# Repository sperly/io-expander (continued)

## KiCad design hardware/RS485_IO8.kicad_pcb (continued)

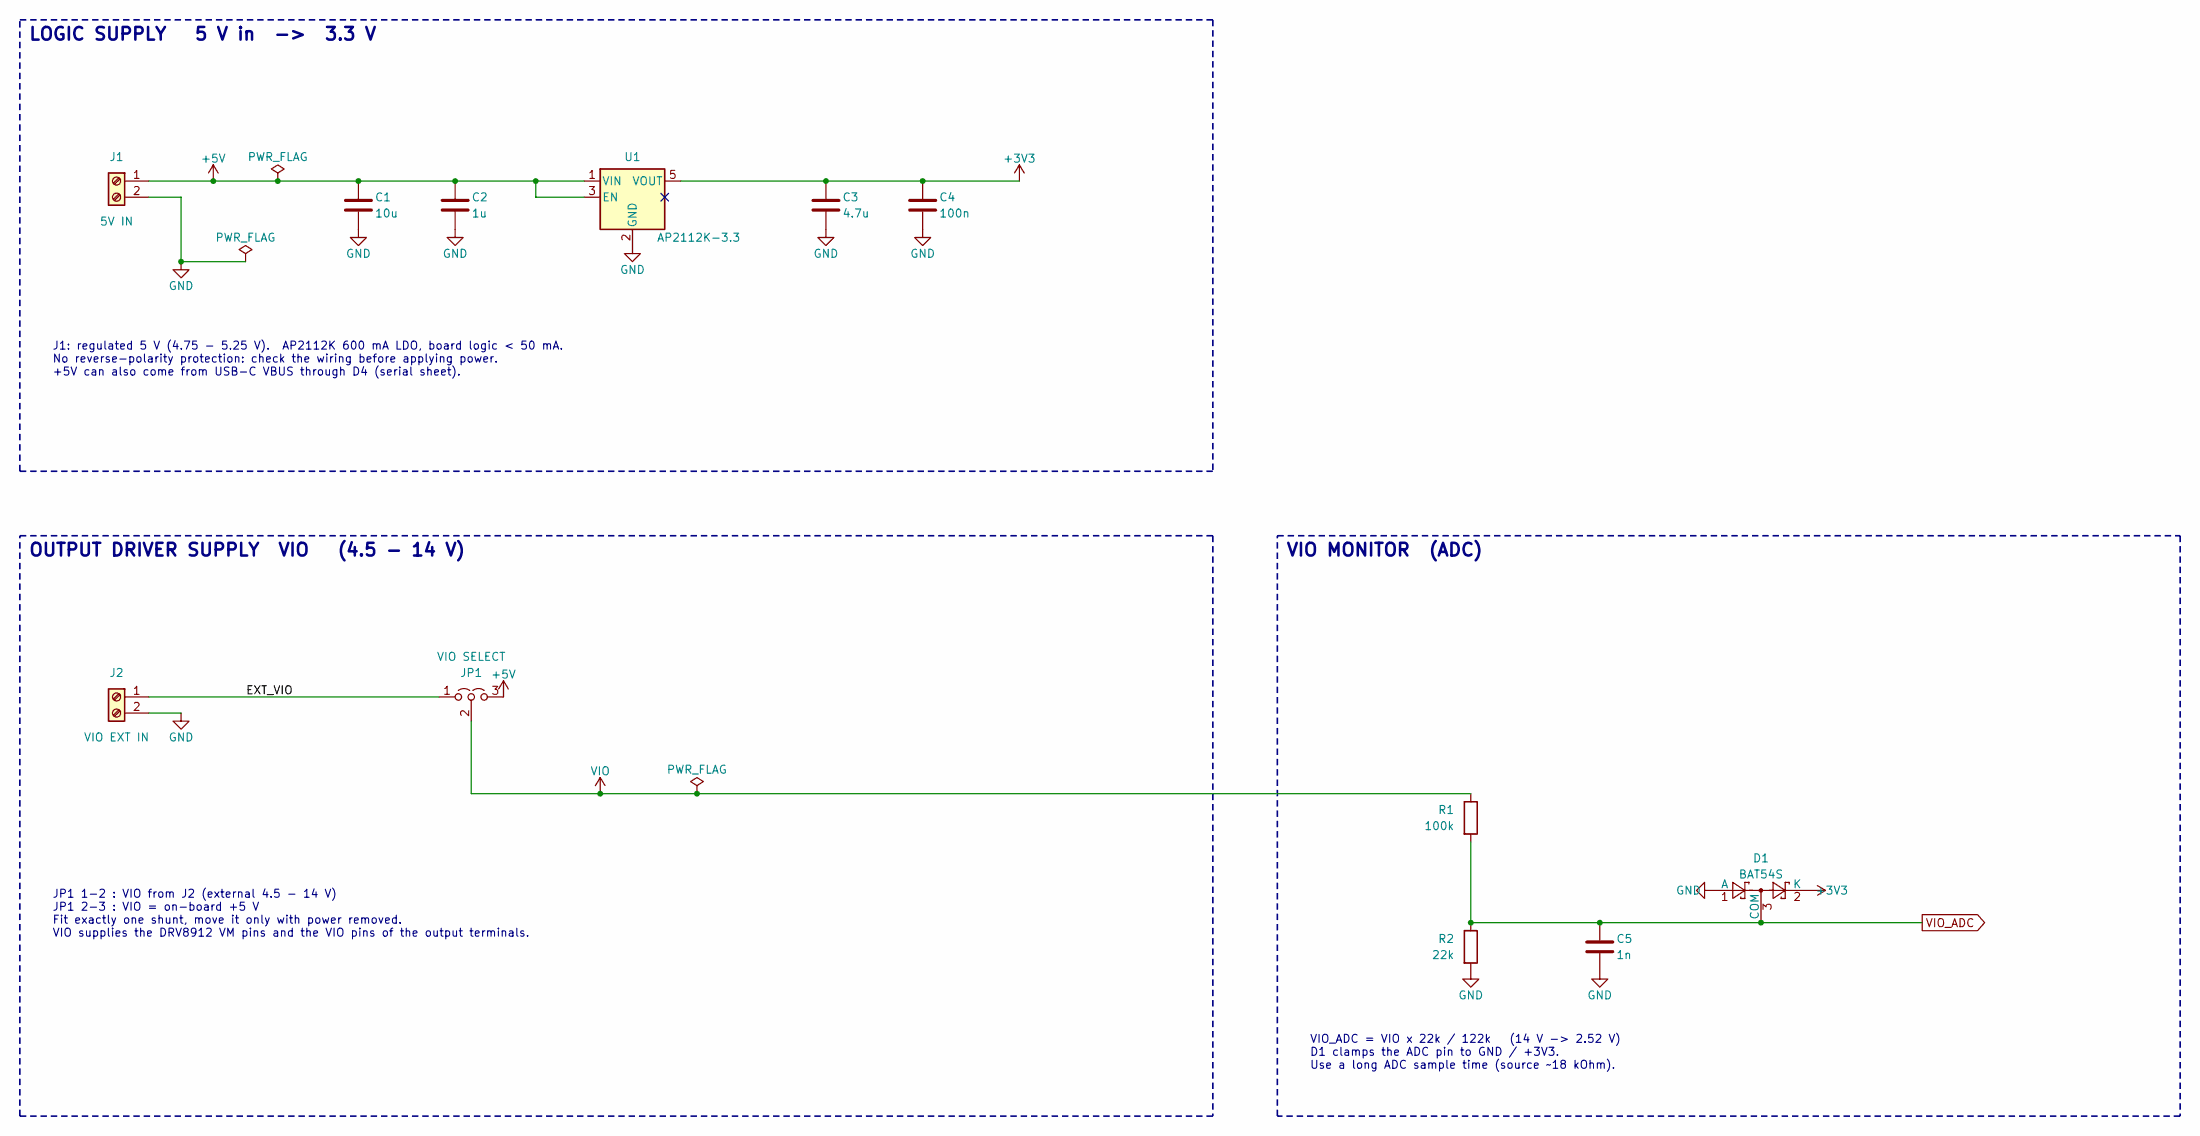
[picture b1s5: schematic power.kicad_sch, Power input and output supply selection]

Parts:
C1: 10u; C_0805_2012Metric; MPN CL21A106KAYNNNE; LCSC C15850
C2: 1u; C_0603_1608Metric; MPN CL10A105KB8NNNC; LCSC C15849
C3: 4.7u; C_0805_2012Metric; MPN CL21A475KAQNNNE; LCSC C1779
C4: 100n; C_0603_1608Metric; MPN CC0603KRX7R9BB104; LCSC C14663
C5: 1n; C_0603_1608Metric; MPN CL10B102KB8NNNC; LCSC C1588
D1: BAT54S; SOT-23; MPN BAT54S; LCSC C7420333
J1: 5V IN; TerminalBlock_Xinya_XY308-2.54-2P_1x02_P2.54mm_Horizontal; MPN XY308-2.54-2P; LCSC C557685
J2: VIO EXT IN; TerminalBlock_Xinya_XY308-2.54-2P_1x02_P2.54mm_Horizontal; MPN XY308-2.54-2P; LCSC C557685
JP1: VIO SELECT; PinHeader_1x03_P2.54mm_Vertical; MPN 2.54-1*3P; LCSC C49257
R1: 100k; R_0603_1608Metric; MPN 0603WAF1003T5E; LCSC C25803
R2: 22k; R_0603_1608Metric; MPN 0603WAF2202T5E; LCSC C31850
U1: AP2112K-3.3; SOT-23-5; MPN AP2112K-3.3TRG1; LCSC C51118

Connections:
+3V3: C3.1, C4.1, D1.2 (K), U1.5 (VOUT); also elsewhere on the board
/Power input and output supply selection/EXT_VIO: J2.1, JP1.1 (A)
VIO_ADC: C5.1, D1.3 (COM), R1.2, R2.1; also elsewhere on the board

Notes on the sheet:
J1: regulated 5 V (4.75 - 5.25 V). AP2112K 600 mA LDO, board logic < 50 mA. No reverse-polarity protection: check the wiring before applying power. +5V can also come from USB-C VBUS through D4 (serial sheet).
LOGIC SUPPLY 5 V in -> 3.3 V
VIO MONITOR (ADC)
VIO_ADC = VIO x 22k / 122k (14 V -> 2.52 V) D1 clamps the ADC pin to GND / +3V3. Use a long ADC sample time (source ~18 kOhm).
JP1 1-2 : VIO from J2 (external 4.5 - 14 V) JP1 2-3 : VIO = on-board +5 V Fit exactly one shunt, move it only with power removed. VIO supplies the DRV8912 VM pins and the VIO pins of the output terminals.
OUTPUT DRIVER SUPPLY VIO (4.5 - 14 V)

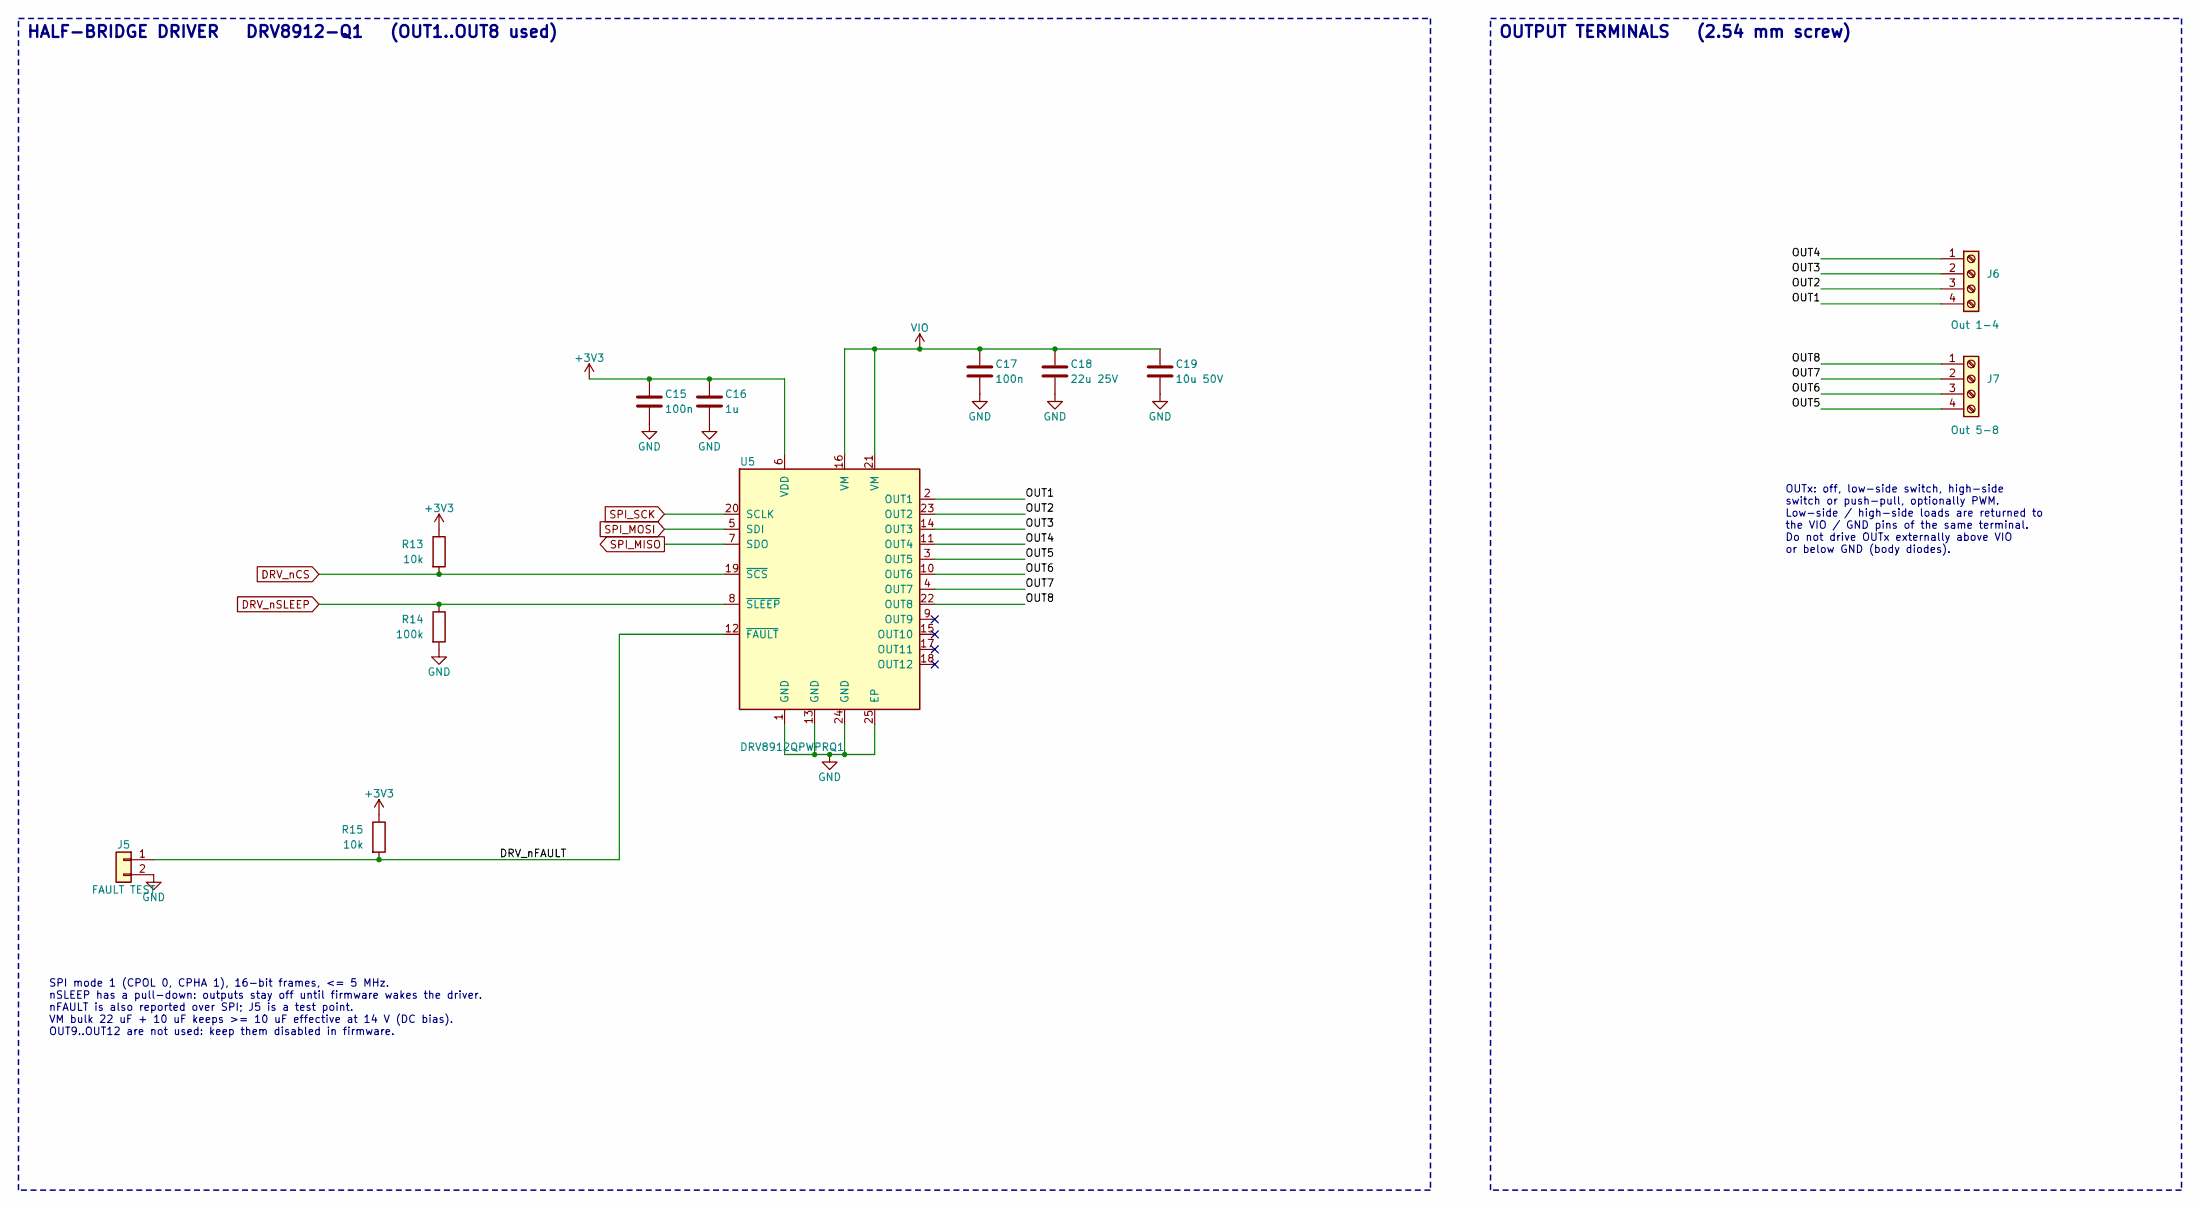
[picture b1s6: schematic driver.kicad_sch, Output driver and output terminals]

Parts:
C15, C17: 100n; C_0603_1608Metric; MPN CC0603KRX7R9BB104; LCSC C14663
C16: 1u; C_0603_1608Metric; MPN CL10A105KB8NNNC; LCSC C15849
C18: 22u 25V; C_1206_3216Metric; MPN CL31A226KAHNNNE; LCSC C12891
C19: 10u 50V; C_1206_3216Metric; MPN CL31A106KBHNNNE; LCSC C13585
J5: FAULT TEST; PinHeader_1x02_P2.54mm_Vertical; MPN PZ254V-11-02P; LCSC C492401
J6: Out 1-4; TerminalBlock_Xinya_XY308-2.54-4P_1x04_P2.54mm_Horizontal
J7: Out 5-8; TerminalBlock_Xinya_XY308-2.54-4P_1x04_P2.54mm_Horizontal
R13, R15: 10k; R_0603_1608Metric; MPN 0603WAF1002T5E; LCSC C25804
R14: 100k; R_0603_1608Metric; MPN 0603WAF1003T5E; LCSC C25803
U5: DRV8912QPWPRQ1; HTSSOP-24-1EP_4.4x7.8mm_P0.65mm_EP3.4x7.8mm_Mask2.4x4.68mm_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; MPN DRV8912QPWPRQ1; LCSC C1855817

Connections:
+3V3: C15.1, C16.1, R13.1, R15.1, U5.6 (VDD); also elsewhere on the board
/Output driver and output terminals/DRV_nFAULT: J5.1, R15.2, U5.12 (~FAULT)
/Output driver and output terminals/OUT1: J6.4, U5.2 (OUT1)
/Output driver and output terminals/OUT2: J6.3, U5.23 (OUT2)
/Output driver and output terminals/OUT3: J6.2, U5.14 (OUT3)
/Output driver and output terminals/OUT4: J6.1, U5.11 (OUT4)
/Output driver and output terminals/OUT5: J7.4, U5.3 (OUT5)
/Output driver and output terminals/OUT6: J7.3, U5.10 (OUT6)
/Output driver and output terminals/OUT7: J7.2, U5.4 (OUT7)
/Output driver and output terminals/OUT8: J7.1, U5.22 (OUT8)
DRV_nCS: R13.2, U5.19 (~SCS); also elsewhere on the board
DRV_nSLEEP: R14.1, U5.8 (~SLEEP); also elsewhere on the board
SPI_MISO: U5.7 (SDO); also elsewhere on the board
SPI_MOSI: U5.5 (SDI); also elsewhere on the board
SPI_SCK: U5.20 (SCLK); also elsewhere on the board

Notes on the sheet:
OUTPUT TERMINALS (2.54 mm screw)
OUTx: off, low-side switch, high-side switch or push-pull, optionally PWM. Low-side / high-side loads are returned to the VIO / GND pins of the same terminal. Do not drive OUTx externally above VIO or below GND (body diodes).
SPI mode 1 (CPOL 0, CPHA 1), 16-bit frames, <= 5 MHz. nSLEEP has a pull-down: outputs stay off until firmware wakes the driver. nFAULT is also reported over SPI; J5 is a test point. VM bulk 22 uF + 10 uF keeps >= 10 uF effective at 14 V (DC bias). OUT9..OUT12 are not used: keep them disabled in fir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
HALF-BRIDGE DRIVER DRV8912-Q1 (OUT1..OUT8 used)

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
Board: 4 copper layers, 105 parts (0 on the bottom side), 79 nets, no tracks yet.

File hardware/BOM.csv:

Designator,Qty,Value,Spec,Footprint,LCSC,MPN,Manufacturer,Library,Stock,Unit price USD
C1,1,10u,25V X5R 0805,Capacitor_SMD:C_0805_2012Metric,C15850,CL21A106KAYNNNE,Samsung,Basic,3710191,0.0692
"C2,C16,C21,C22",4,1u,50V X5R 0603,Capacitor_SMD:C_0603_1608Metric,C15849,CL10A105KB8NNNC,Samsung,Basic,9868521,0.0152
C3,1,4.7u,25V X5R 0805,Capacitor_SMD:C_0805_2012Metric,C1779,CL21A475KAQNNNE,Samsung,Basic,2469579,0.0348
"C4,C6,C8,C9,C10,C11,C12,C13,C14,C15,C17,C20,C23",13,100n,50V X7R 0603,Capacitor_SMD:C_0603_1608Metric,C14663,CC0603KRX7R9BB104,YAGEO,Basic,50349394,0.0141
C5,1,1n,50V X7R 0603,Capacitor_SMD:C_0603_1608Metric,C1588,CL10B102KB8NNNC,Samsung,Basic,6432787,0.009
C7,1,4.7u,16V X5R 0603,Capacitor_SMD:C_0603_1608Metric,C19666,CL10A475KO8NNNC,Samsung,Basic,2948420,0.0297
C18,1,22u 25V,25V X5R 1206,Capacitor_SMD:C_1206_3216Metric,C12891,CL31A226KAHNNNE,Samsung,Basic,553006,0.1174
C19,1,10u 50V,50V X5R 1206,Capacitor_SMD:C_1206_3216Metric,C13585,CL31A106KBHNNNE,Samsung,Basic,2368794,0.2882
D1,1,BAT54S,"dual Schottky, series",Package_TO_SOT_SMD:SOT-23,C7420333,BAT54S,CJ,Preferred,1074536,0.0138
D2,1,SM712,RS-485 TVS -7/+12V,Package_TO_SOT_SMD:SOT-23,C7420375,SM712,Hongjiacheng,Preferred,538546,0.0727
D3,1,15V TVS,bidirectional 15V,Diode_SMD:D_SOD-323,C20615813,H15VND3B,Hongjiacheng,Preferred,802787,0.0363
D4,1,B5819W,Schottky 40V 1A SOD-123,Diode_SMD:D_SOD-123,C8598,B5819W SL,CJ,Basic,384842,0.0284
D5,1,BAT54A,"dual Schottky, common anode",Package_TO_SOT_SMD:SOT-23,C130910,"BAT54A,215",Nexperia,Extended,149225,0.0225
"J1,J2",2,"5V IN,VIO EXT IN",screw terminal 2P 2.54mm,TerminalBlock:TerminalBlock_Xinya_XY308-2.54-2P_1x02_P2.54mm_Horizontal,C557685,XY308-2.54-2P,Xinya,Extended,5635,0.2485
J3,1,SWD,pin header 2x5 1.27mm,Connector_PinHeader_1.27mm:PinHeader_2x05_P1.27mm_Vertical,C41426986,A127M01-0B10P51-H10A39,HanElectricity,Extended,10501,0.0504
J4,1,SERIAL,screw terminal 4P 2.54mm,TerminalBlock:TerminalBlock_Xinya_XY308-2.54-4P_1x04_P2.54mm_Horizontal,C915913,XY308-2.54-4P,Xinya,Extended,5011,0.4967
"J5,JP2,JP3,JP4,JP5,JP6,JP7",7,"ADDR0,ADDR1,BIAS A,BIAS B,FAULT TEST,MODE,TERM",pin header 1x2 2.54mm,Connector_PinHeader_2.54mm:PinHeader_1x02_P2.54mm_Vertical,C492401,PZ254V-11-02P,XFCN,Extended,1088237,0.0187
"J6,J7",2,"OUT1-OUT4,OUT5-OUT8",screw terminal 6P 2.54mm,TerminalBlock:TerminalBlock_Xinya_XY308-2.54-6P_1x06_P2.54mm_Horizontal,C915915,XY308-2.54-6P,Xinya,Extended,1072,0.6754
"J8,J9",2,"IN1-IN4 COM1,IN5-IN8 COM2",screw terminal 5P 2.54mm,TerminalBlock:TerminalBlock_Xinya_XY308-2.54-5P_1x05_P2.54mm_Horizontal,C915914,XY308-2.54-5P,Xinya,Extended,6330,0.6262
J10,1,DB9 SERIAL,"D-Sub 9 female, right angle",Connector_Dsub:DSUB-9_Socket_Horizontal_P2.77x2.84mm_EdgePinOffset7.70mm_Housed_MountingHolesOffset9.12mm,C141882,D-DMR009PF-D002,Ckmtw,Extended,47298,0.459
J11,1,USB-C,"USB Type-C receptacle 16P (USB 2.0), SMD right angle",Connector_USB:USB_C_Receptacle_HRO_TYPE-C-31-M-12,C165948,TYPE-C-31-M-12,HRO,Extended,367975,0.1872
JP1,1,VIO SELECT,pin header 1x3 2.54mm,Connector_PinHeader_2.54mm:PinHeader_1x03_P2.54mm_Vertical,C49257,2.54-1*3P,BOOMELE,Extended,253882,0.0284
"R1,R14",2,100k,1% 0.1W 0603,Resistor_SMD:R_0603_1608Metric,C25803,0603WAF1003T5E,UNI-ROYAL,Basic,19748113,0.0031
"R2,R18,R21,R24,R27,R30,R33,R36,R39",9,22k,1% 0.1W 0603,Resistor_SMD:R_0603_1608Metric,C31850,0603WAF2202T5E,UNI-ROYAL,Basic,3458604,0.0042
"R3,R6,R7,R8,R9,R13,R15,R40,R41",9,10k,1% 0.1W 0603,Resistor_SMD:R_0603_1608Metric,C25804,0603WAF1002T5E,UNI-ROYAL,Basic,32380385,0.0052
"R4,R5,R17,R20,R23,R26,R29,R32,R35,R38,R44",11,4.7k,1% 0.1W 0603,Resistor_SMD:R_0603_1608Metric,C23162,0603WAF4701T5E,UNI-ROYAL,Basic,19500720,0.0028
R10,1,120R,1% 0.25W 1206,Resistor_SMD:R_1206_3216Metric,C17909,1206W4F1200T5E,UNI-ROYAL,Basic,451968,0.0069
"R11,R12",2,390R,1% 0.1W 0603,Resistor_SMD:R_0603_1608Metric,C23151,0603WAF3900T5E,UNI-ROYAL,Basic,2397325,0.0017
"R16,R19,R22,R25,R28,R31,R34,R37",8,3.3k,1% 0.25W 1206,Resistor_SMD:R_1206_3216Metric,C26032,1206W4F3301T5E,UNI-ROYAL,Extended,214556,0.005
"R42,R43",2,5.1k,1% 0.1W 0603,Resistor_SMD:R_0603_1608Metric,C23186,0603WAF5101T5E,UNI-ROYAL,Basic,23749760,0.0015
U1,1,AP2112K-3.3,LDO 3.3V 600mA,Package_TO_SOT_SMD:SOT-23-5,C51118,AP2112K-3.3TRG1,Diodes Inc,Extended,12535,0.1724
U2,1,STM32G030F6P6,Cortex-M0+ 32KB TSSOP-20,Package_SO:TSSOP-20_4.4x6.5mm_P0.65mm,C724040,STM32G030F6P6,ST,Extended,2180,1.4884
U3,1,24AA02T-I/OT,2 kbit I2C EEPROM,Package_TO_SOT_SMD:SOT-23-5,C478090,24AA02T-I/OT,Microchip,Extended,608,0.3548
U4,1,MAX3160EAP+T,RS-232/RS-485 multiprotocol transceiver,Package_SO:SSOP-20_5.3x7.2mm_P0.65mm,C406604,MAX3160EAP+T,Analog Devices,Extended,4102,4.8993
U5,1,DRV8912QPWPRQ1,12-ch SPI half-bridge driver,Package_SO:HTSSOP-24-1EP_4.4x7.8mm_P0.65mm_EP3.4x7.8mm_Mask2.4x4.68mm_ThermalVias,C1855817,DRV8912QPWPRQ1,Texas Instruments,Extended,2444,4.0175
"U6,U7",2,TLP290-4,"quad AC-input optocoupler, CTR 100-400 %",Package_SO:SOP-16_4.55x10.3mm_P1.27mm,C39031,"TLP290-4(GB-TP,E",Toshiba,Extended,15882,0.5606
U8,1,MCP23S08T-E/SS,8-bit SPI I/O expander,Package_SO:SSOP-20_5.3x7.2mm_P0.65mm,C145600,MCP23S08T-E/SS,Microchip,Extended,389,1.8063
U9,1,USBLC6-2SC6,"USB ESD protection, 2 lines + VBUS",Package_TO_SOT_SMD:SOT-23-6,C2687116,USBLC6-2SC6,UMW,Extended,58349,0.0479
U10,1,CH340C,"USB to UART, crystal-less, SOP-16",Package_SO:SOIC-16_3.9x9.9mm_P1.27mm,C84681,CH340C,WCH,Extended,124020,0.5459

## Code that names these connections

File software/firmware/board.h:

/*
 * RS485_IO8 rev B pin map (8 isolated inputs, 8 outputs) - STM32G030F6P6 (TSSOP-20).
 * Must match hardware/mcu.kicad_sch.
 *
 *  pin  signal        function
 *   1   PB7           I2C1_SDA (AF6)   24AA02 EEPROM
 *   2   PC14          ADDR0 strap (input, external 10k pull-up, fitted = low)
 *   3   PC15          ADDR1 strap
 *   6   NRST          reset (also resets the MCP23S08)
 *   7   PA0           ADC_IN0  VIO monitor, VIO = Vadc * 122 / 22
 *   8   PA1           SPI1_SCK  (AF0)
 *   9   PA2           SPI1_MOSI (AF0)
 *  10   PA3           IN_IRQ  MCP23S08 INT (opto inputs), open-drain active low (EXTI3)
 *  11   PA4           DRV_nCS
 *  12   PA5           IN_nCS
 *  13   PA6           SPI1_MISO (AF0)
 *  14   PA7           DRV_nSLEEP (external 100k pull-down)
 *  15   PB0           SER_DE  MAX3160 DE485/T2IN (external 10k pull-down)
 *  16   PA9  (remap)  USART1_TX (AF1)  -> MAX3160 DI/T1IN
 *  17   PA10 (remap)  USART1_RX (AF1)  <- MAX3160 RO/R2OUT
 *  18   PA13          SWDIO
 *  19   PA14          SWCLK
 *  20   PB6           I2C1_SCL (AF6)
 *
 * Pads shared by several GPIOs on this package (PB3/4/5/6, PB7/PB8,
 * PB9/PC14, PA8/PB0/PB1/PB2, PA11/PA9, PA12/PA10) - the unused GPIOs keep
 * their reset state (analog mode). LSE is never enabled (PC14/PC15 used).
 */
#ifndef BOARD_H
#define BOARD_H

#include "stm32g0xx.h"

#define SYSCLK_HZ 16000000u /* HSI16, no PLL */

#define PIN_ADDR0_PORT GPIOC
#define PIN_ADDR0 14u
#define PIN_ADDR1_PORT GPIOC
#define PIN_ADDR1 15u

#define PIN_VIO_ADC_PORT GPIOA
#define PIN_VIO_ADC 0u
#define ADC_CH_VIO 0u
#define ADC_CH_VREFINT 13u

#define PIN_SCK 1u   /* GPIOA */
#define PIN_MOSI 2u  /* GPIOA */
#define PIN_MISO 6u  /* GPIOA */
#define PIN_IN_IRQ 3u
#define PIN_DRV_NCS 4u
#define PIN_IN_NCS 5u
#define PIN_DRV_NSLEEP 7u

#define PIN_SER_DE_PORT GPIOB
#define PIN_SER_DE 0u
#define PIN_UART_TX 9u  /* GPIOA, remapped to pad PA11 */
#define PIN_UART_RX 10u /* GPIOA, remapped to pad PA12 */

#define PIN_I2C_SCL 6u /* GPIOB */
#define PIN_I2C_SDA 7u /* GPIOB */

/* VIO divider 100k / 22k */
#define VIO_DIV_NUM 122u
#define VIO_DIV_DEN 22u

#endif

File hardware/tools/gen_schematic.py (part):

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J2 = pw.add("Connector", "Screw_Terminal_01x02", ref("J"), v, g(12), g(50), mirror="y",
            text={"Reference": (0, -3.81, None), "Value": (0, 6.35, None)}, **f)
v, f = cat("HDR3", "VIO SELECT")
f["Description"] = "3-pin strap: 1-2 = external VIO, 2-3 = +5 V"
JP1 = pw.add("Jumper", "Jumper_3_Open", ref("JP"), v, g(34), g(50),
             text={"Reference": (0, -3.81, None), "Value": (0, -6.35, None)}, **f)
pw.wire(J2[1], JP1[1])
pw.label((g(20), g(50)), "EXT_VIO", 0, kind="local")
pw.wire(J2[2], (g(16), g(51)))
pw.power("GND", (g(16), g(51)))
pw.power("+5V", JP1[3])
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pw.note((g(8), g(62)), "JP1 1-2 : VIO from J2 (external 4.5 - 14 V)\n"
        "JP1 2-3 : VIO = on-board +5 V\n"
        "Fit exactly one shunt, move it only with power removed.\n"
        "VIO supplies the DRV8912 VM pins and the VIO pins of the output terminals.")

pw.frame(g(84), g(40), g(140), g(76), "VIO MONITOR  (ADC)")
r1 = R(pw, "100k", g(96), g(56) + 3.81, left_text=True)
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            text={"Reference": (0, -5.08, None), "Value": (0, -2.54, None)}, **f)
pw.power("GND", D1[1], rot=270)
pw.power("+3V3", D1[2], rot=270)
pw.label((g(124), g(64)), "VIO_ADC", 0, shape="output")
pw.note((g(86), g(71)), "VIO_ADC = VIO x 22k / 122k   (14 V -> 2.52 V)\n"
        "D1 clamps the ADC pin to GND / +3V3.\n"
        "Use a long ADC sample time (source ~18 kOhm).")
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mc.stub(U2[2], "ADDR0", "left", g(5), kind="local")
mc.table((g(62), g(56)), [
    ("Pin", "Function", "Pin", "Function"),
    ("PA0", "VIO monitor (ADC_IN0)", "PA7", "driver nSLEEP"),
    ("PA1/PA2/PA6", "SPI1 SCK/MOSI/MISO", "PB0", "transceiver DE"),
    ("PA3", "expander IRQ (EXTI3)", "PA9/PA10", "USART1 TX/RX (remap PA11/12)"),
    ("PA4", "driver nCS", "PB6/PB7", "I2C1 SCL/SDA"),
    ("PA5", "expander nCS", "PC14/PC15", "address straps"),
], widths=[g(7), g(10), g(6), g(10)])

mc.frame(g(6), g(8), g(56), g(30), "RESET")
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mc.wire(U3[5], (g(12), g(48)))
mc.power("GND", (g(12), g(48)))
mc.wire(U3[3], (g(24), g(47)), (g(24), g(40)), (g(44), g(40)))   # SDA
mc.label((g(44), g(40)), "I2C_SDA", 0, kind="local")
pullup(mc, "4k7", g(32), g(40))
mc.wire(U3[1], (g(44), g(48)))                                    # SCL
mc.label((g(44), g(48)), "I2C_SCL", 0, kind="local")
pullup(mc, "4k7", g(38), g(48))

mc.frame(g(6), g(58), g(56), g(84), "ADDRESS STRAPS")
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se.label((g(46), ym), "MODE", 0, kind="local")
yd = U4[15][1]
se.wire(U4[15], (g(28), yd))
se.label((g(28), yd), "SER_DE", 180, shape="input")
pulldown(se, "10k", g(44), yd, left_text=True)
se.table((g(8), g(62)), [
    ("MODE strap", "Interface", "J4 pins used"),
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se.wire(U4[5], (g(80), U4[5][1]), (g(80), yB), (g(127), yB))
se.wire(U4[13], (g(76), U4[13][1]), (g(76), yR), (g(131), yR))
se.nc(U4[14])
se.label((g(84), yA), "LINE_A", 0, kind="local")
se.label((g(84), yB), "LINE_B_TXD", 0, kind="local")
se.label((g(84), yR), "LINE_RXD", 0, kind="local")

se.frame(g(92), g(8), g(150), g(80), "PROTECTION, TERMINATION, BIAS, TERMINAL")
v, f = cat("SM712")
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se.power("GND", J10["SH"])
for p_ in (4, 7, 8, 9):
    se.nc(J10[p_])
se.stub(J10[6], "DB9_PIN6", "right", g(2), kind="local")
jp8 = se.add("Jumper", "SolderJumper_2_Bridged", "JP8", "5V ON PIN 6", g(140), g(62),
             text={"Reference": (0, -2.54, None), "Value": (0, 2.54, None)},
             Footprint="Jumper:SolderJumper-2_P1.3mm_Bridged_RoundedPad1.0x1.5mm",
             Description="Cut to remove +5 V from DB9 pin 6", _nobom=True)
se.wire((jp8[1][0] - g(2), jp8[1][1]), jp8[1])
se.label((jp8[1][0] - g(2), jp8[1][1]), "DB9_PIN6", 180, kind="local")
se.wire(jp8[2], (jp8[2][0] + g(2), jp8[2][1]))
se.power("+5V", (jp8[2][0] + g(2), jp8[2][1]))
se.table((g(94), g(48)), [
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dr.stub(U5[7], "SPI_MISO", "left", g(4), shape="output")
y = U5[19][1]
dr.wire(U5[19], (g(26), y))
dr.label((g(26), y), "DRV_nCS", 180, shape="input")
pullup(dr, "10k", g(34), y, left_text=True)
y = U5[8][1]
dr.wire(U5[8], (g(26), y))
dr.label((g(26), y), "DRV_nSLEEP", 180, shape="input")
pulldown(dr, "100k", g(34), y, left_text=True)
y = U5[12][1]
dr.wire(U5[12], (g(46), y), (g(46), g(64)), (g(16), g(64)))
dr.label((g(38), g(64)), "DRV_nFAULT", 0, kind="local")
pullup(dr, "10k", g(30), g(64), left_text=True)
v, f = cat("HDR2", "FAULT TEST")
f["Description"] = "Test point: 1 = nFAULT, 2 = GND"
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dr.note((g(106), g(66)), "OUTx: off, low-side switch, high-side\n"
        "switch or push-pull, optionally PWM.\n"
        "Low-side / high-side loads are returned to\n"
        "the VIO / GND pins of the same terminal.\n"
        "Do not drive OUTx externally above VIO\n"
        "or below GND (body diodes).")

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ins.stub(U6[6], "NRST", "left", g(3))
y = U6[7][1]
ins.wire(U6[7], (g(112), y))
ins.label((g(112), y), "IN_nCS", 180, shape="input")
pullup(ins, "10k", g(118), y, left_text=True)
y = U6[8][1]
ins.wire(U6[8], (g(112), y))
ins.label((g(112), y), "IN_IRQ", 180, shape="output")
pullup(ins, "10k", g(118), y, left_text=True)
ins.power("GND", U6[4], rot=270)
ins.power("GND", U6[5], rot=270)
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se.wire(J11["A6"], U10[3])
se.stub(U10[6], "USB_DM", "right", g(3), kind="local")
se.stub(U10[4], "USB_DP", "right", g(3), kind="local")
se.label((g(23), J11["A7"][1]), "USB_DM", 0, kind="local")
se.label((g(23), J11["A6"][1]), "USB_DP", 0, kind="local")
se.power("GND", U10[2])
se.power("GND", J11["A1"])
se.wire(J11["SH"], J11["A1"])
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D5 = se.add("Diode", "BAT54A", ref("D"), v, g(73), g(89),
            text={"Reference": (0, -3.81, None), "Value": (2.54, 3.81, "left")}, **f)
se.wire(U9[2], (g(66), U9[2][1]), (g(66), D5[1][1]), D5[1])
se.label((g(66), D5[1][1]), "USB_TXD", 180, kind="local")
se.stub(D5[2], "MAX_RO", "right", g(3), kind="local")
yr = g(97)
se.wire(D5[3], (D5[3][0], yr), (g(86), yr))
pullup(se, "4k7", g(80), yr)
se.label((g(86), yr), "UART_RX", 0, shape="output")
se.note((g(64), g(102)), "CC1 / CC2 5.1k: USB device, up to 500 mA from VBUS.\n"
        "D4: USB VBUS -> +5V (about 4.6 V); J1 and USB may be connected together.\n"
        "UART_RX = MAX3160 RO AND CH340C TXD (D5, 4.7k pull-up): both host links\n"
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
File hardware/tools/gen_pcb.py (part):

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    "U9": (112.0, 152.0, 0), "C22": (112.0, 155.2, 0), "D4": (116.5, 151.2, 0),
    "R42": (116.6, 154.0, 0), "R43": (116.6, 156.0, 0),
    "U10": (130.6, 153.55, 90), "C23": (123.8, 152.0, 90),
    # wired-AND on UART_RX, next to the MAX3160 RO pin
    "D5": (122.5, 127.0, 0), "R44": (126.5, 127.0, 0),
    # ---- transceiver
    "U4": (124.0, 118.0, 0),
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    "U1": (122.0, 148.0, 0),
    "C3": (126.5, 148.0, 90), "C4": (129.5, 148.0, 90),
    "JP1": (124.8, 108.6, 90),                              # VIO select, next to J2 on the top edge
    # VIO monitor divider + clamp, next to the ADC input (U2 pin 7)
    "R1": (130.0, 128.7, 90), "R2": (131.8, 128.7, 90), "C5": (133.6, 128.7, 90), "D1": (132.0, 132.0, 0),
    # ---- MCU
    "U2": (145.0, 128.0, 0),
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            else:                  # vertical label above the terminal
                silk(board, name, x, BOT_ROW - 4.1, 0.8, angle=90, justify="left")

    pin_labels("J6", ["GND", "VIO", "OUT4", "OUT3", "OUT2", "OUT1"], "top")
    pin_labels("J7", ["GND", "VIO", "OUT8", "OUT7", "OUT6", "OUT5"], "top")
    pin_labels("J8", ["IN1", "IN2", "IN3", "IN4", "COM1"], "bottom")
    pin_labels("J9", ["IN5", "IN6", "IN7", "IN8", "COM2"], "bottom")
    pin_labels("J4", ["A", "B/TXD", "RXD", "GND"], "bottom")
    pin_labels("J1", ["+5V", "GND"], "bottom")
    pin_labels("J2", ["VIO", "GND"], "top")
    # terminal and J11 references are hidden: the pin labels and the USB-C shape identify them
    fps["R41"].Reference().SetPosition(mm(166.4, 130.5))  # R40 / R41 sit side by side
    for ref in ("U6", "U7", "U8", "U10"):  # reference inside the body (clear of the barrier line / caps)
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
